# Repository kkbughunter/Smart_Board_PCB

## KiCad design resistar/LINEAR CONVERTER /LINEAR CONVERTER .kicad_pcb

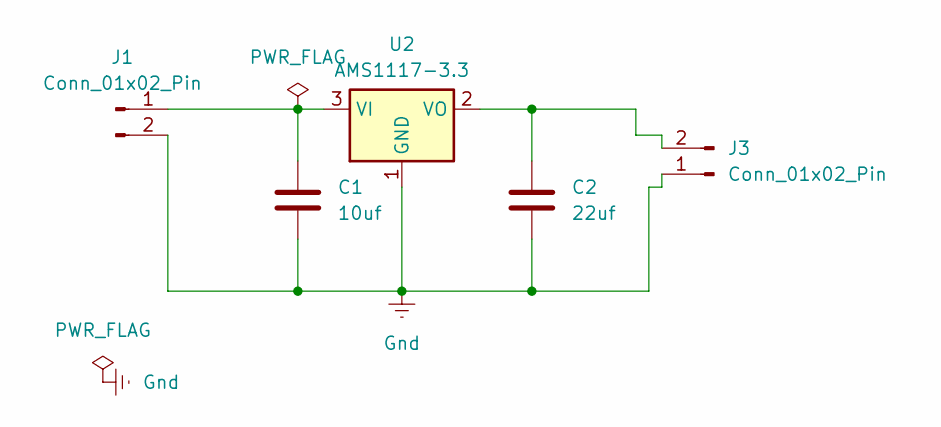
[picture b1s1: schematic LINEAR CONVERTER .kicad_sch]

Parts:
C1: 10uf; C_0805_2012Metric_Pad1.18x1.45mm_HandSolder
C2: 22uf; C_1206_3216Metric
J1: Conn_01x02_Pin; PinHeader_1x02_P2.54mm_Horizontal
J3: Conn_01x02_Pin; PinHeader_1x02_P2.54mm_Vertical
U2: AMS1117-3.3; SOT-223-3_TabPin2

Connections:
Gnd: C1.2, C2.2, J1.2, J3.1, U2.1 (GND)
unnamed: C1.1, J1.1, U2.3 (VI)
unnamed: C2.1, J3.2, U2.2 (VO)

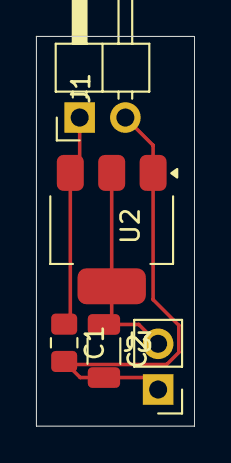
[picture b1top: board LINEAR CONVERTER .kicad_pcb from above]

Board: 2 copper layers, 8.8 x 21.7 mm, 5 parts (0 on the bottom side), 3 nets.

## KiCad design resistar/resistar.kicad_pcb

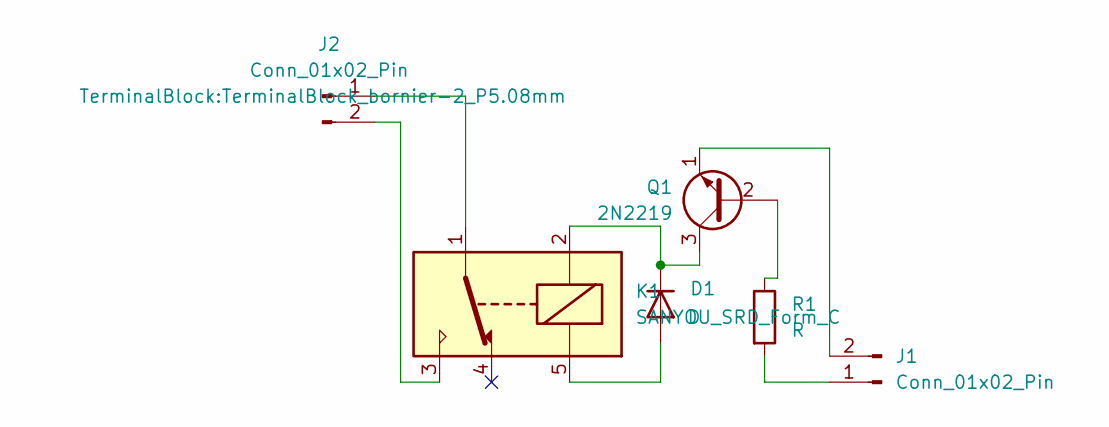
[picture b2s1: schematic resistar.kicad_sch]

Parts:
D1: D; D_A-405_P7.62mm_Horizontal
J1: Conn_01x02_Pin; TerminalBlock_Xinya_XY308-2.54-2P_1x02_P2.54mm_Horizontal
J2: Conn_01x02_Pin; TerminalBlock_bornier-2_P5.08mm
K1: SANYOU_SRD_Form_C; Relay_SPDT_SANYOU_SRD_Series_Form_C
Q1: 2N2219; TO-92_Inline
R1: R; R_Axial_DIN0204_L3.6mm_D1.6mm_P7.62mm_Horizontal

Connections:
unnamed: D1.2 (A), K1.5
unnamed: D1.1 (K), K1.2, Q1.3 (C)
unnamed: J1.1, R1.2
unnamed: J1.2, Q1.1 (E)
unnamed: J2.1, K1.1
unnamed: J2.2, K1.3
unnamed: Q1.2 (B), R1.1

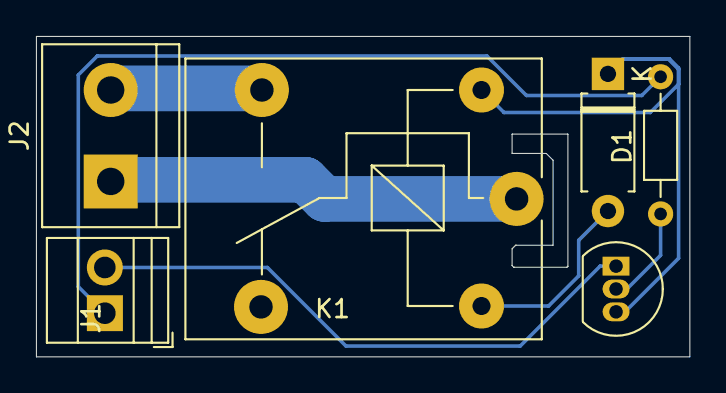
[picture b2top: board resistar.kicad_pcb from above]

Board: 2 copper layers, 36.3 x 17.8 mm, 6 parts (0 on the bottom side), 7 nets.

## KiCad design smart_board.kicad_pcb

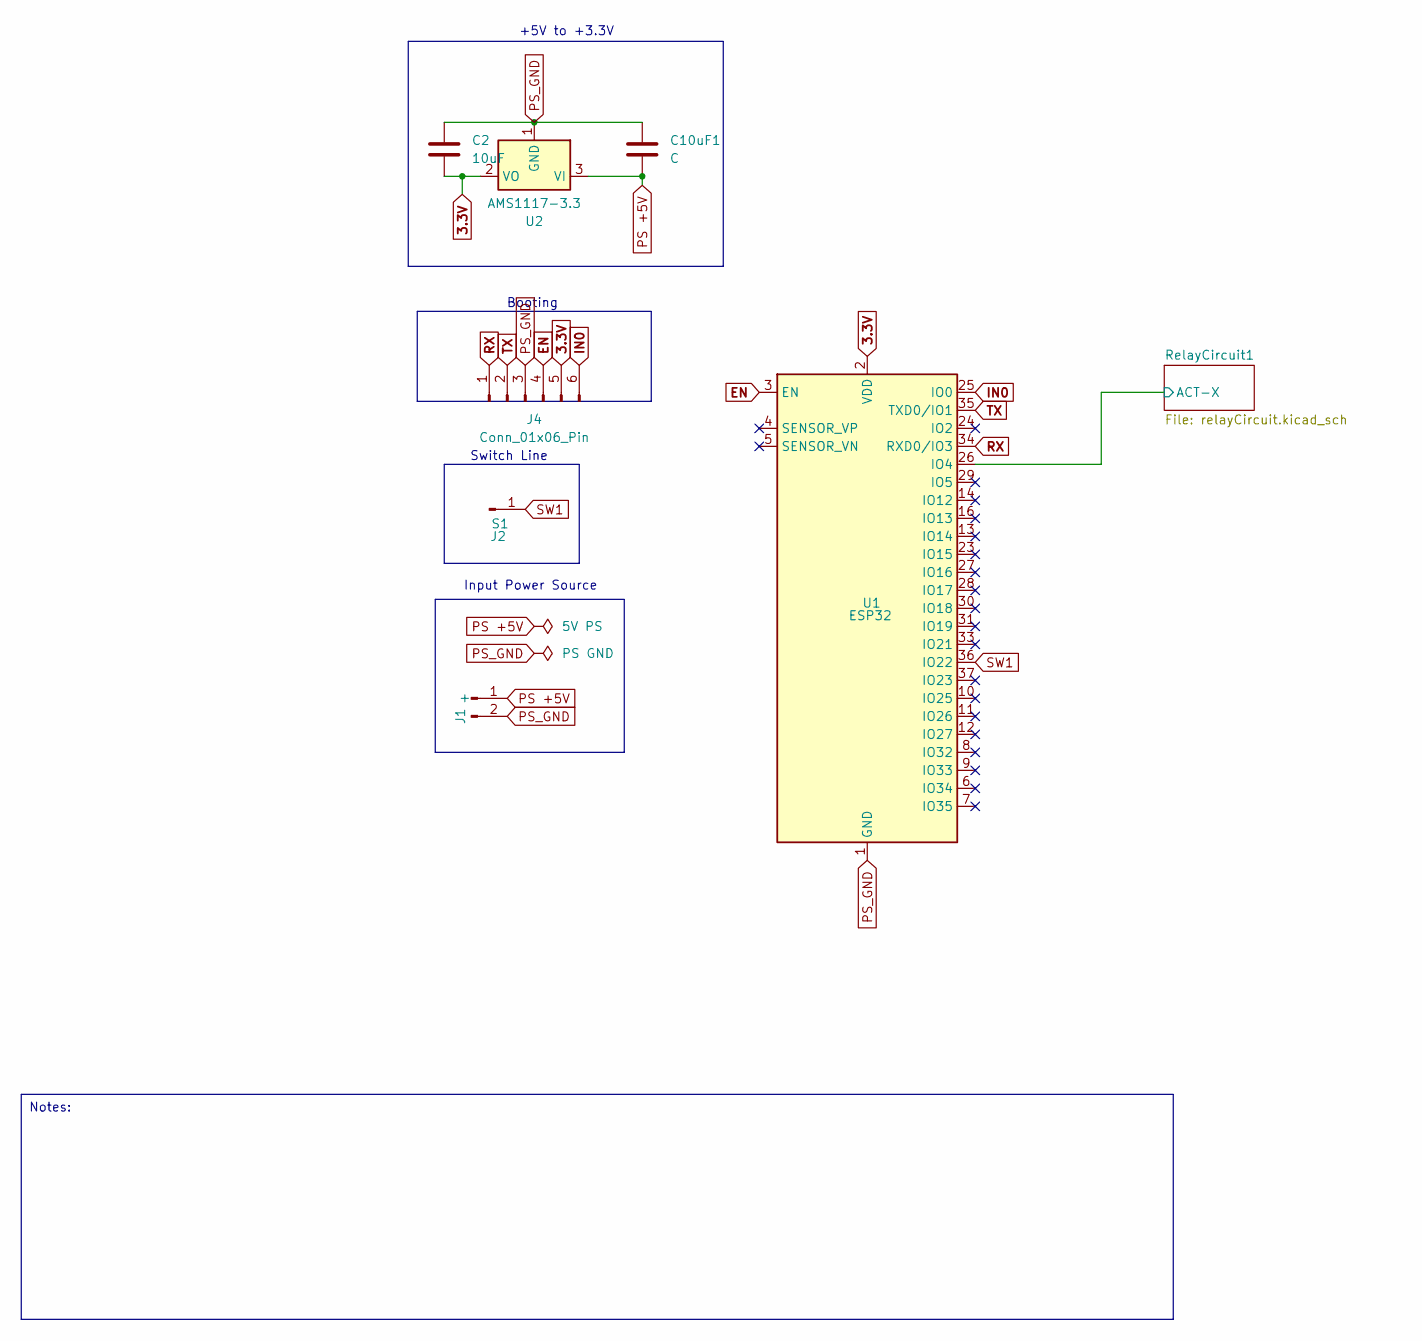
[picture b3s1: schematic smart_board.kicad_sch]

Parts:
C2: 10uF; C_0603_1608Metric_Pad1.08x0.95mm_HandSolder
C10uF1: C; C_0603_1608Metric_Pad1.08x0.95mm_HandSolder
J1: +; TerminalBlock_Phoenix_MPT-0,5-2-2.54_1x02_P2.54mm_Horizontal
J2: S1; PinHeader_1x01_P2.54mm_Vertical
J4: Conn_01x06_Pin; PinHeader_2x03_P2.54mm_Vertical
U1: ESP32; ESP32-WROOM-32D
U2: AMS1117-3.3; SOT-223-3_TabPin2

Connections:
3.3V: C2.1, J4.5, U1.2 (VDD), U2.2 (VO)
/RelayCircuit1/ACT-X: U1.26 (IO4); also elsewhere on the board
EN: J4.4, U1.3 (EN)
IN0: J4.6, U1.25 (IO0)
PS +5V: C10uF1.1, J1.1, U2.3 (VI); also elsewhere on the board
PS_GND: C2.2, C10uF1.2, J1.2, J4.3, U1.1 (GND), U1.15 (GND), U1.38 (GND), U1.39 (GND), U2.1 (GND); also elsewhere on the board
RX: J4.1, U1.34 (RXD0/IO3)
SW1: J2.1, U1.36 (IO22)
TX: J4.2, U1.35 (TXD0/IO1)

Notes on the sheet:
Notes:
Booting
Input Power Source
Switch Line
+5V to +3.3V

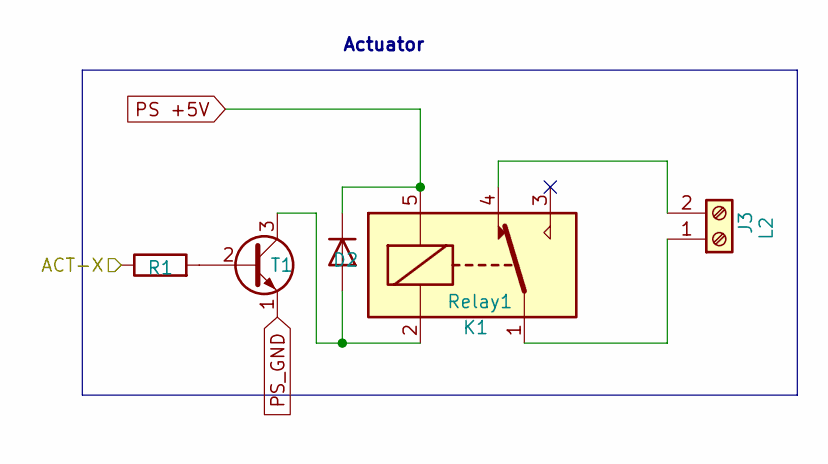
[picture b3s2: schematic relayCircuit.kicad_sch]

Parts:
D2: 1N4007; D_DO-35_SOD27_P7.62mm_Horizontal
J3: L2; TerminalBlock_Phoenix_MKDS-1,5-2-5.08_1x02_P5.08mm_Horizont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
K1: Relay1; Relay_SPDT_SANYOU_SRD_Series_Form_C
R1: 1KΩ; R_Axial_DIN0207_L6.3mm_D2.5mm_P7.62mm_Horizontal
T1: 2N2222; TO-92_Inline

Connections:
/RelayCircuit1/ACT-X: R1.1; also elsewhere on the board
unnamed: D2.2 (A), K1.2, T1.3 (C)
unnamed: J3.1, K1.1
unnamed: J3.2, K1.4
unnamed: R1.2, T1.2 (B)
PS +5V: D2.1 (K), K1.5; also elsewhere on the board
PS_GND: T1.1 (E); also elsewhere on the board

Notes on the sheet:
Actuator

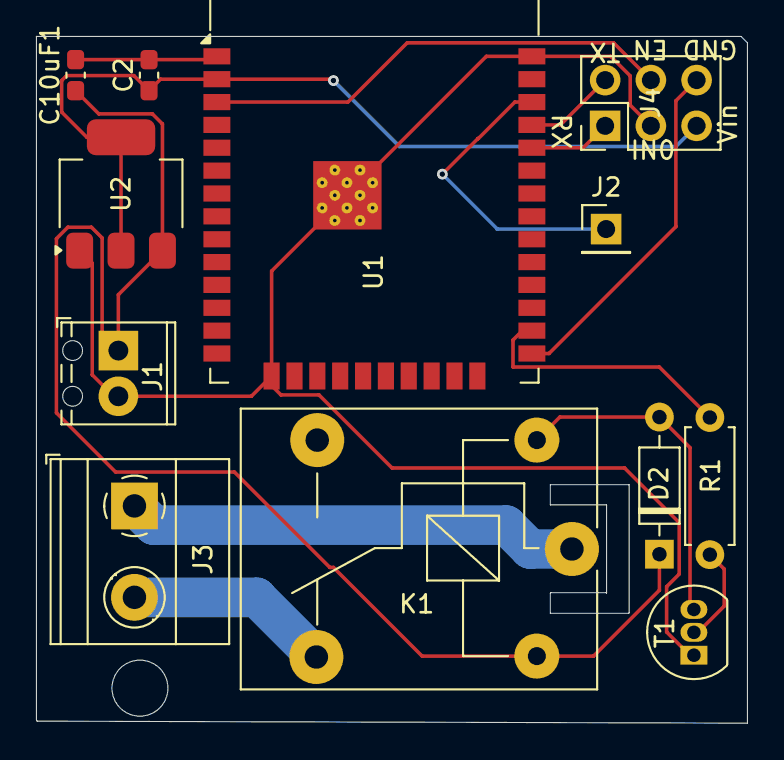
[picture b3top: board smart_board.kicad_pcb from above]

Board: 2 copper layers, 39.5 x 38.2 mm, 12 parts (0 on the bottom side), 13 nets.

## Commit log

2025-06-05 Single Node Smart Board PCB Design
